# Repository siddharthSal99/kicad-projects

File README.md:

clock: particle photon rgb led strip command strip
ATTINY Bootloader: arduino shield for bootloading the attiny 85
Blinky: pcb that an rgb led strip can be plugged into to control color
Transistor Clock: Clock that is controlled purely by transistor logic to count and time the circuit.

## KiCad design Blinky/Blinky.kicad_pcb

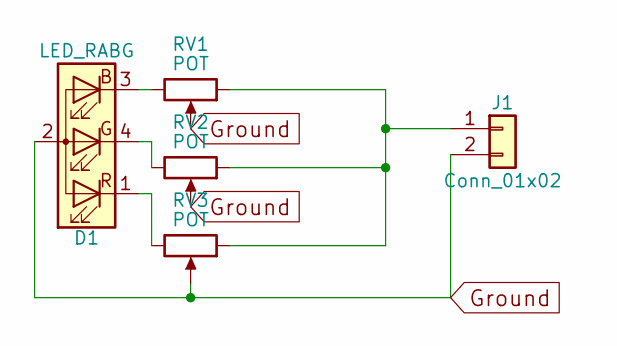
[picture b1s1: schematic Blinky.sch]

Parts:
D1: LED_RABG; Pin_Header_Straight_1x04_Pitch2.54mm
J1: Conn_01x02; Pin_Header_Straight_1x02_Pitch2.54mm
RV1, RV2, RV3: POT; Potentiometer_Trimmer_Vishay_T73YP_Horizontal

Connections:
Ground: D1.2 (A), J1.2, RV1.2, RV2.2, RV3.2
unnamed: D1.1 (RK), RV3.3
unnamed: D1.3 (BK), RV1.3
unnamed: D1.4 (GK), RV2.3
unnamed: J1.1, RV1.1, RV2.1, RV3.1

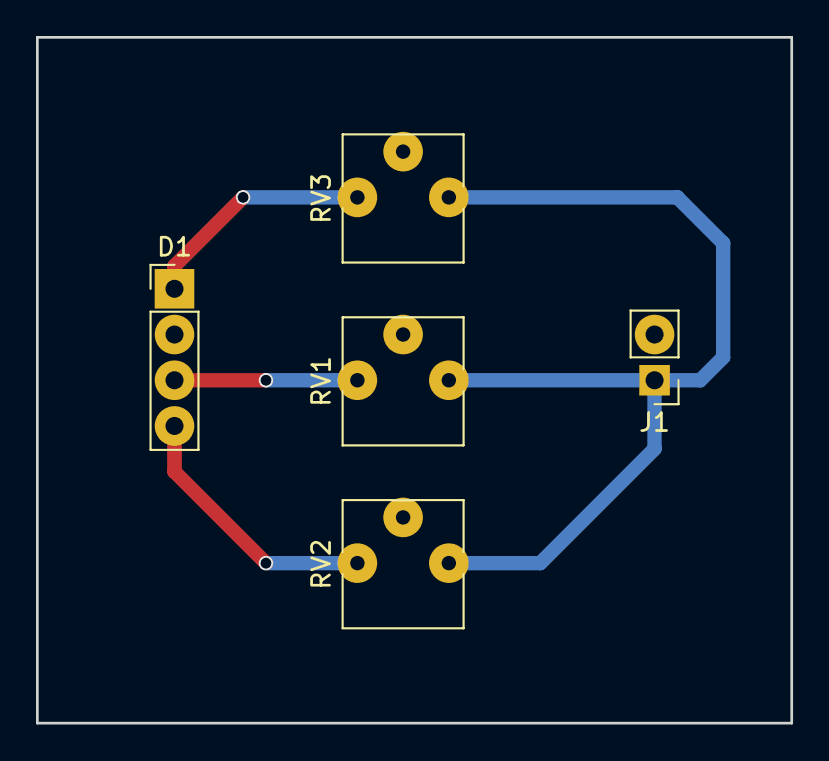
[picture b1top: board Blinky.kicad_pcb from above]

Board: 2 copper layers, 41.9 x 38.1 mm, 5 parts (0 on the bottom side), 5 nets.

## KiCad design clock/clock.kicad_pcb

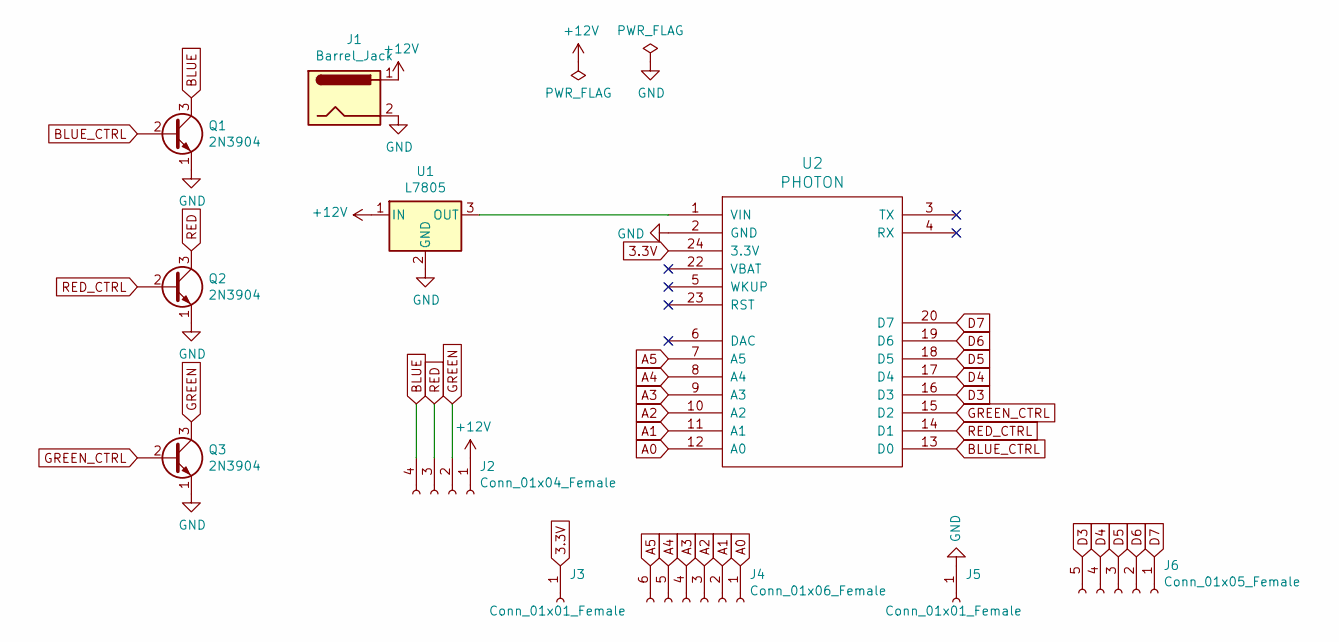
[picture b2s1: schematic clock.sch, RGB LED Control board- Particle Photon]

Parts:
J1: Barrel_Jack; BARREL_JACK
J2: Conn_01x04_Female; Pin_Header_Straight_1x04_Pitch2.54mm
J3, J5: Conn_01x01_Female; Pin_Header_Straight_1x01_Pitch2.54mm
J4: Conn_01x06_Female; Pin_Header_Straight_1x06_Pitch2.54mm
J6: Conn_01x05_Female; Pin_Header_Straight_1x05_Pitch2.54mm
Q1, Q2, Q3: 2N3904; TO-92_Inline_Narrow_Oval
U1: L7805; Pin_Header_Straight_1x03_Pitch2.54mm
U2: PHOTON

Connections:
3.3V: J3.1, U2.24 (3.3V)
+12V: J1.1, J2.1, U1.1 (IN)
A0: J4.1, U2.12 (A0)
A1: J4.2, U2.11 (A1)
A2: J4.3, U2.10 (A2)
A3: J4.4, U2.9 (A3)
A4: J4.5, U2.8 (A4)
A5: J4.6, U2.7 (A5)
BLUE: J2.4, Q1.3 (C)
BLUE_CTRL: Q1.2 (B), U2.13 (D0)
D3: J6.5, U2.16 (D3)
D4: J6.4, U2.17 (D4)
D5: J6.3, U2.18 (D5)
D6: J6.2, U2.19 (D6)
D7: J6.1, U2.20 (D7)
GND: J1.2, J5.1, Q1.1 (E), Q2.1 (E), Q3.1 (E), U1.2 (GND), U2.2 (GND)
GREEN: J2.2, Q3.3 (C)
GREEN_CTRL: Q3.2 (B), U2.15 (D2)
unnamed: U1.3 (OUT), U2.1 (VIN)
RED: J2.3, Q2.3 (C)
RED_CTRL: Q2.2 (B), U2.14 (D1)

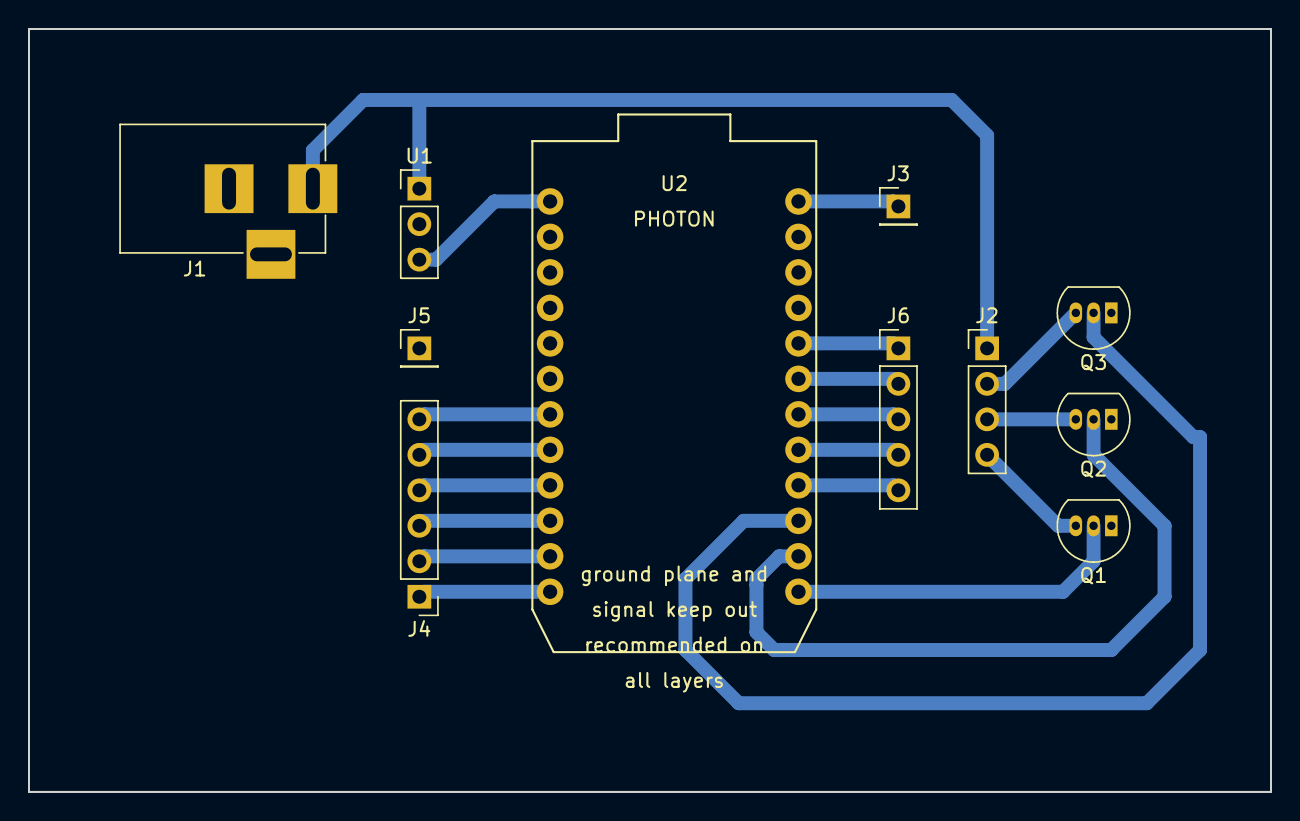
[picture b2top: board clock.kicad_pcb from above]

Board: 2 copper layers, 88.9 x 54.6 mm, 11 parts (0 on the bottom side), 21 nets.

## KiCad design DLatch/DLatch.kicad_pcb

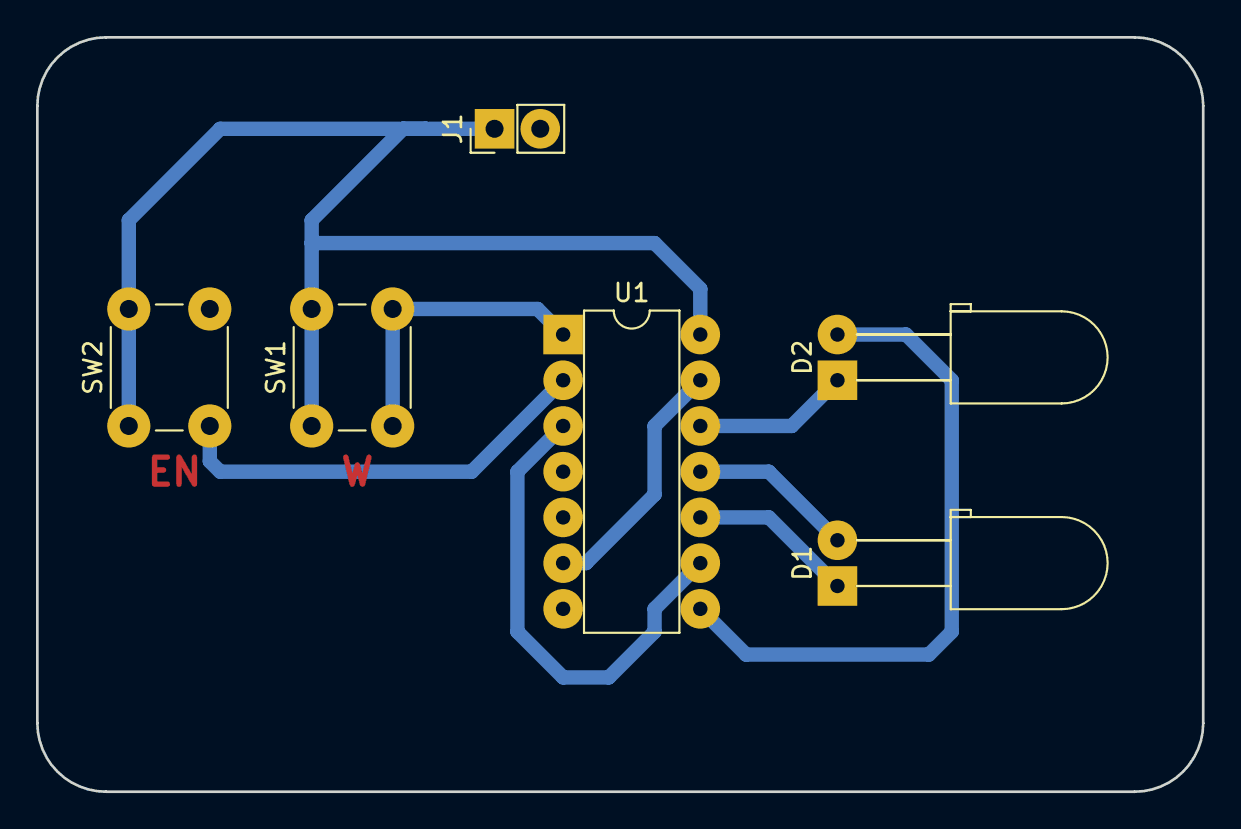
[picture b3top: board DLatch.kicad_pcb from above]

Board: 2 copper layers, 64.8 x 41.9 mm, 6 parts (0 on the bottom side), 10 nets.

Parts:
D1, D2: LED; LED_D5.0mm_Horizontal_O6.35mm_Z9.0mm
J1: Conn_01x02; Pin_Header_Straight_1x02_Pitch2.54mm
SW1, SW2: SW_Push; SW_PUSH_6mm_h13mm
U1: 7400; DIP-14_W7.62mm

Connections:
+5V: J1.1, SW1.1, SW2.1, U1.14
GND: J1.e2, U1.7
unnamed: D1.1, U1.10
unnamed: D1.2, U1.11
unnamed: D2.e1, U1.12
unnamed: D2.2, U1.8
unnamed: SW1.2, U1.1, U1.5
unnamed: SW2.2, U1.2, U1.4
unnamed: U1.3, U1.9
unnamed: U1.6, U1.13

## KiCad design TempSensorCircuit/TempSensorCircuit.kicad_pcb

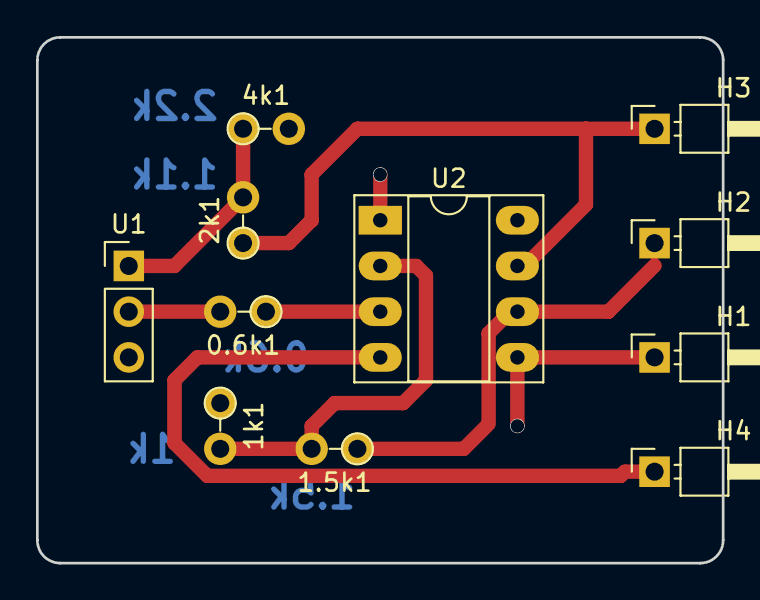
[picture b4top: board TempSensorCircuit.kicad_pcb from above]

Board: 2 copper layers, 38.1 x 29.2 mm, 11 parts (0 on the bottom side), 8 nets.

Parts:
0.6k1, 1.5k1, 1k1, 2k1, 4k1: R; R_Axial_DIN0204_L3.6mm_D1.6mm_P2.54mm_Vertical
H1, H2, H3, H4: MountingHole_Pad; Pin_Header_Angled_1x01_Pitch2.54mm
U1: LM32; Pin_Header_Straight_1x03_Pitch2.54mm
U2: LM741; DIP-8_W7.62mm_Socket_LongPads

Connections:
+12V: 2k1.1, H3.1, U2.7
-12V: H4.1, U2.4
GND: 1k1.1, 4k1.2, H1.1, U1.3, U2.1, U2.5
unnamed: 0.6k1.1, U2.3
unnamed: 0.6k1.2, U1.2
unnamed: 1.5k1.e, H2.1, U2.6
unnamed: 1.5k1.2, 1k1.2, U2.2
unnamed: 2k1.2, 4k1.e, U1.1

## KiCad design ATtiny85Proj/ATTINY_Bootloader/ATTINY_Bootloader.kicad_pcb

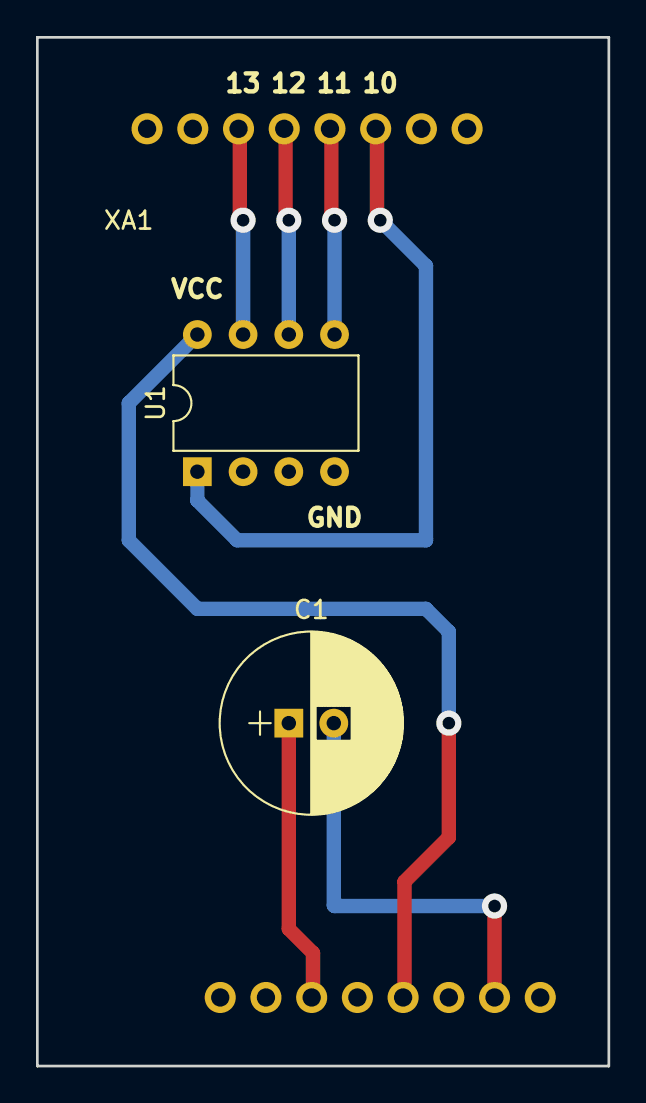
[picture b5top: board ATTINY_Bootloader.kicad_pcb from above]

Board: 2 copper layers, 31.8 x 57.2 mm, 3 parts (0 on the bottom side), 7 nets.

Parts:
C1: C; CP_Radial_D10.0mm_P2.50mm
U1: ATtiny85-20PU; DIP-8_W7.62mm
XA1: Arduino_Uno_Shield_ATTINY_Bootloader

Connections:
+5V: U1.8, XA1.5V1
GND: C1.2, U1.4, XA1.GND3
unnamed: C1.1, XA1.RST1
PIN10_PIN1: U1.1, XA1.D10
PIN11_PIN5: U1.5, XA1.D11
PIN12_PIN6: U1.6, XA1.D12
PIN13_PIN7: U1.7, XA1.D13

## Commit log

2019-09-20 Added projects from invention studio: ATTINY bootloader, particle photon rgb control board, rgb control circuit, Transistor clock circuit
2019-09-20 Added readme describing projects
2019-10-15 Switch board light project and temperature sensor conversion circuit project
